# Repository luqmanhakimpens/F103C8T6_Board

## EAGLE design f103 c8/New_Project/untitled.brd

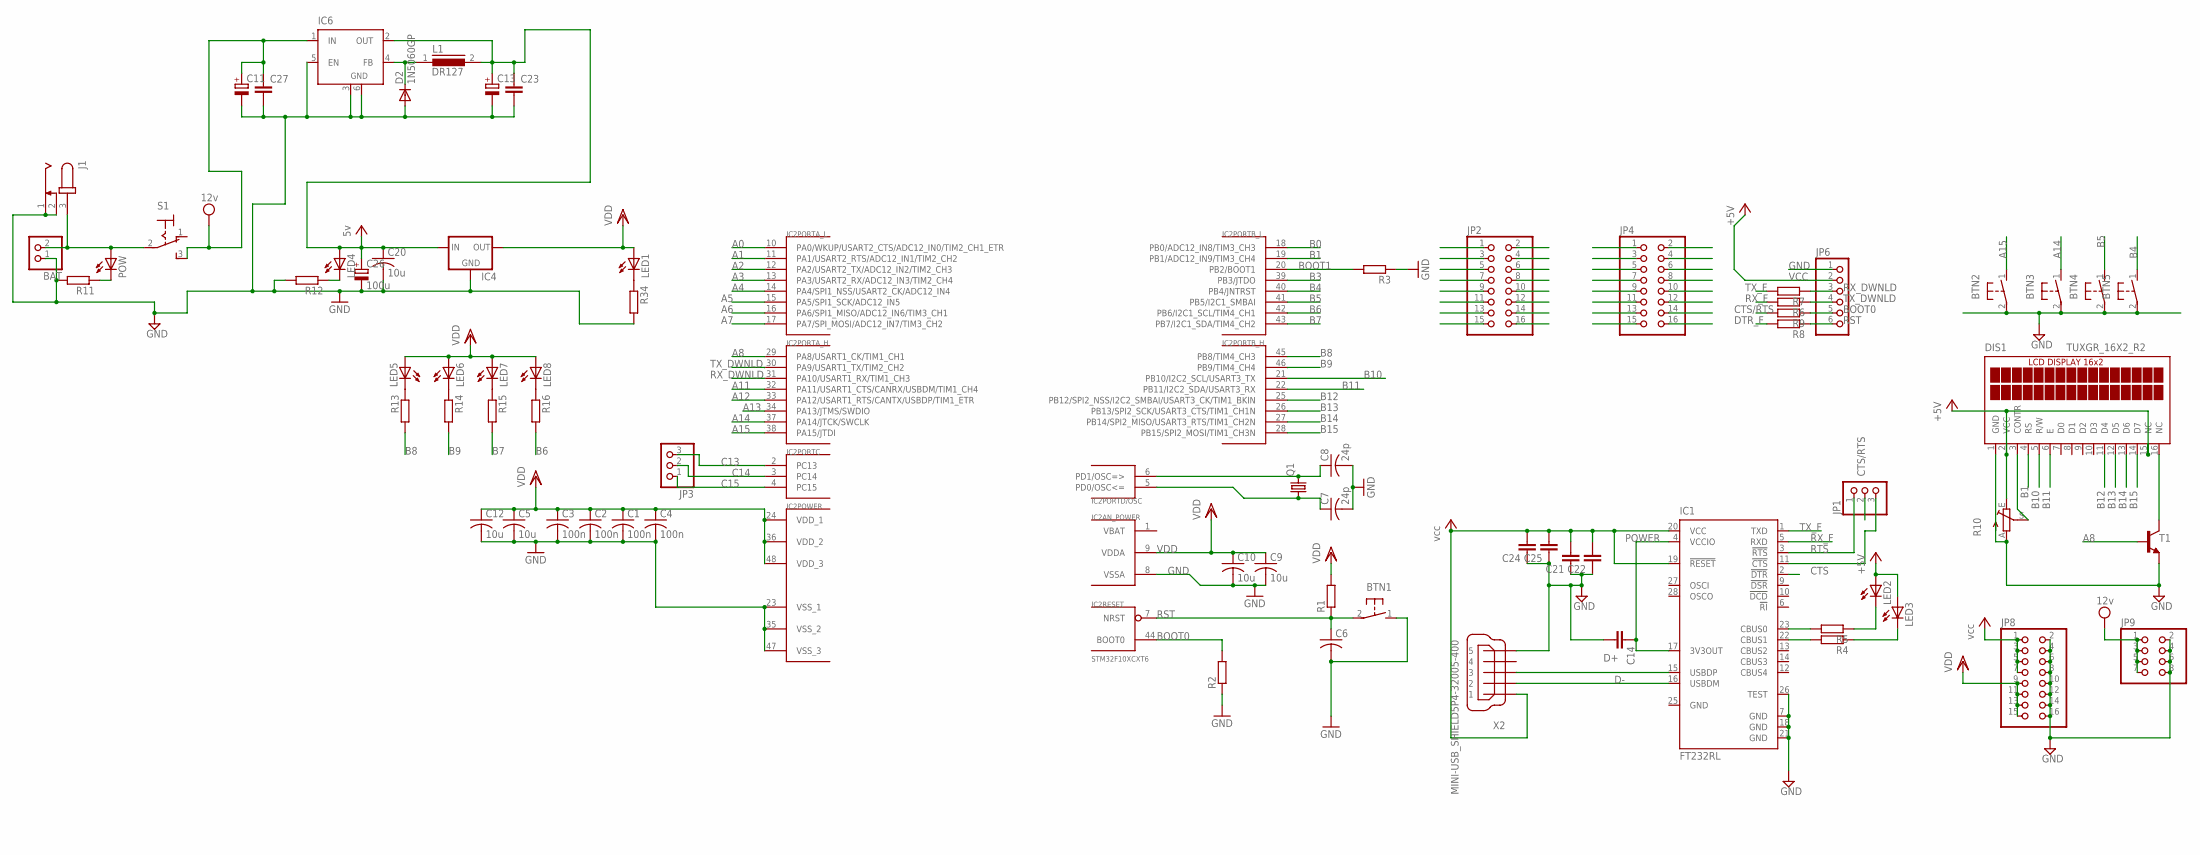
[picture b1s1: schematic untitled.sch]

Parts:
BAT: PINHD-1X2; 1X02
BTN1, BTN2, BTN3, BTN4, BTN5: PUSHBTN; PUSHBUTTON
C1, C2, C3, C4: 100n; C0805
C5, C9, C10, C12, C20: 10u; C0805
C6: C-USC0805; C0805
C7, C8: 24p; C0805
C11, C13: CPOL-EU153CLV-1012; 153CLV-1012
C14, C21, C22, C23, C24, C25, C27: C-EUC0805; C0805
C26: 100u; 153CLV-1012
D2: 1N5060GP; DO15-12
DIS1: TUXGR_16X2_R2
IC1: FT232RL; SSOP28
IC2: STM32F10XCXT6; TQFP48
IC4: LM1117; SOT223
IC6: LM2596S; TO263-5
J1: JACK-PLUG1; SPC4078
JP1, JP3: PINHD-1X3; 1X03
JP2, JP4, JP8: PINHD-2X8; 2X08
JP6: PINHD-1X6; 1X06
JP9: PINHD-2X4; 2X04
L1: DR127
LED1, LED2, LED3, LED4, LED5, LED6, LED7, LED8: LEDSMT1206; 1206
POW: LEDSMT1206; 1206
Q1: CRYSTALHC49U-V; HC49U-V
R1, R2, R3, R11, R12, R13, R14, R15, R16, R34: R-EU_M0805; M0805
R4, R5, R6, R7, R8, R9: R-EU_R0805; R0805
R10: TRIM_EU-CA6V; CA6V
S1: 320-916
T1: BC818-NPN-SOT23-BEC; SOT23-BEC
X2: MINI-USB_SHIELD5P4-32005-400; 32005-400

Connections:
12V: C11.+, C27.1, IC6.1 (IN), JP9.1, JP9.3, JP9.5, JP9.7, S1.3 (S)
A0: IC2.10 (PA0/WKUP/USART2_CTS/ADC12_IN0/TIM2_CH1_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)
A1: IC2.11 (PA1/USART2_RTS/ADC12_IN1/TIM2_CH2)
A2: IC2.12 (PA2/USART2_TX/ADC12_IN2/TIM2_CH3)
A3: IC2.13 (PA3/USART2_RX/ADC12_IN3/TIM2_CH4)
A4: IC2.14 (PA4/SPI1_NSS/USART2_CK/ADC12_IN4)
A5: IC2.15 (PA5/SPI1_SCK/ADC12_IN5)
A6: IC2.16 (PA6/SPI1_MISO/ADC12_IN6/TIM3_CH1)
A7: IC2.17 (PA7/SPI_MOSI/ADC12_IN7/TIM3_CH2)
A8: IC2.29 (PA8/USART1_CK/TIM1_CH1), T1.B
A11: IC2.32 (PA11/USART1_CTS/CANRX/USBDM/TIM1_CH4)
A12: IC2.33 (PA12/USART1_RTS/CANTX/USBDP/TIM1_ETR)
A13: IC2.34 (PA13/JTMS/SWDIO)
A14: BTN3.1, IC2.37 (PA14/JTCK/SWCLK)
A15: BTN2.1, IC2.38 (PA15/JTDI)
B0: IC2.18 (PB0/ADC12_IN8/TIM3_CH3)
B1: DIS1.4 (RS), IC2.19 (PB1/ADC12_IN9/TIM3_CH4)
B3: IC2.39 (PB3/JTDO)
B4: BTN5.1, IC2.40 (PB4/JNTRST)
B5: BTN4.1, IC2.41 (PB5/I2C1_SMBAI)
B6: IC2.42 (PB6/I2C1_SCL/TIM4_CH1), R16.2
B7: IC2.43 (PB7/I2C1_SDA/TIM4_CH2), R15.2
B8: IC2.45 (PB8/TIM4_CH3), R13.2
B9: IC2.46 (PB9/TIM4_CH4), R14.2
B10: DIS1.5 (R/W), IC2.21 (PB10/I2C2_SCL/USART3_TX)
B11: DIS1.6 (E), IC2.22 (PB11/I2C2_SDA/USART3_RX)
B12: DIS1.11 (D4), IC2.25 (PB12/SPI2_NSS/I2C2_SMBAI/USART3_CK/TIM1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)
B13: DIS1.12 (D5), IC2.26 (PB13/SPI2_SCK/USART3_CTS/TIM1_CH1N)
B14: DIS1.13 (D6), IC2.27 (PB14/SPI2_MISO/USART3_RTS/TIM1_CH2N)
B15: DIS1.14 (D7), IC2.28 (PB15/SPI2_MOSI/TIM1_CH3N)
BOOT0: IC2.44 (BOOT0), JP6.5, R2.2, R9.1
BOOT1: IC2.20 (PB2/BOOT1), R3.2
C13: IC2.2 (PC13), JP3.3
C14: IC2.3 (PC14), JP3.2
C15: IC2.4 (PC15), JP3.1
CTS: IC1.11 (!CTS), JP1.3
CTS/RTS: JP1.2, R9.2
D+: IC1.15 (USBDP), X2.3
D-: IC1.16 (USBDM), X2.2
DTR_F: IC1.2 (!DTR), R8.2
GND: BAT.1, BTN1.1, BTN2.2, BTN3.2, BTN4.2, BTN5.2, C1.2, C2.2, C3.2, C4.2, C5.2, C6.2, C7.2, C8.2, C9.2, C10.2, C11.-, C12.2, C13.-, C14.2, C20.2, C21.1, C22.1, C23.2, C24.1, C25.1, C26.-, C27.2, D2.A, DIS1.1 (GND), IC1.7 (GND), IC1.18 (GND), IC1.21 (GND), IC1.25 (GND), IC1.26 (TEST), IC2.8 (VSSA), IC2.23 (VSS_1), IC2.35 (VSS_2), IC2.47 (VSS_3), IC4.1 (GND), IC6.3 (GND), IC6.5 (EN), IC6.6 (GND), J1.1, J1.2, JP6.1, JP8.2, JP8.4, JP8.6, JP8.8, JP8.10, JP8.12, JP8.14, JP8.16, JP9.2, JP9.4, JP9.6, JP9.8, R2.1, R3.1, R10.A, R11.2, R12.2, R34.2, T1.E, X2.5
unnamed: LED2.C, R5.1
unnamed: LED3.C, R4.1
unnamed: BAT.2, J1.3, POW.A, S1.2
unnamed: IC1.23 (CBUS0), R5.2
unnamed: IC1.22 (CBUS1), R4.2
unnamed: LED4.C, R12.1
unnamed: DIS1.3 (CONTR), R10.S
unnamed: LED5.C, R13.1
unnamed: LED6.C, R14.1
unnamed: LED7.C, R15.1
unnamed: LED8.C, R16.1
unnamed: DIS1.16 (NC), T1.C
unnamed: D2.C, IC6.4 (FB), L1.1
unnamed: POW.C, R11.1
unnamed: LED1.C, R34.1
OSC_IN: C7.1, IC2.5 (PD0/OSC<=), Q1.1
OSC_OUT: C8.1, IC2.6 (PD1/OSC=>), Q1.2
POWER: C14.1, IC1.4 (VCCIO), IC1.17 (3V3OUT)
RST: BTN1.2, C6.1, IC2.7 (NRST), JP6.6, R1.1, R8.1
RTS: IC1.3 (!RTS), JP1.1
RX_DWNLD: IC2.31 (PA10/USART1_RX/TIM1_CH3), JP6.3, R7.1
RX_F: IC1.5 (RXD), R6.2
TX_DWNLD: IC2.30 (PA9/USART1_TX/TIM2_CH2), JP6.4, R6.1
TX_F: IC1.1 (TXD), R7.2
VBAT: IC2.1 (VBAT)
VCC: C13.+, C20.1, C21.2, C22.2, C23.1, C24.2, C25.2, C26.+, IC1.19 (!RESET), IC1.20 (VCC), IC4.3 (IN), IC6.2 (OUT), JP6.2, JP8.1, JP8.3, JP8.5, JP8.7, L1.2, LED2.A, LED3.A, LED4.A, X2.1
VDD: C1.1, C2.1, C3.1, C4.1, C5.1, C9.1, C10.1, C12.1, DIS1.2 (VCC), DIS1.15 (NC), IC2.9 (VDDA), IC2.24 (VDD_1), IC2.36 (VDD_2), IC2.48 (VDD_3), IC4.2 (OUT), JP8.9, JP8.11, JP8.13, JP8.15, LED1.A, LED5.A, LED6.A, LED7.A, LED8.A, R1.2, R10.E

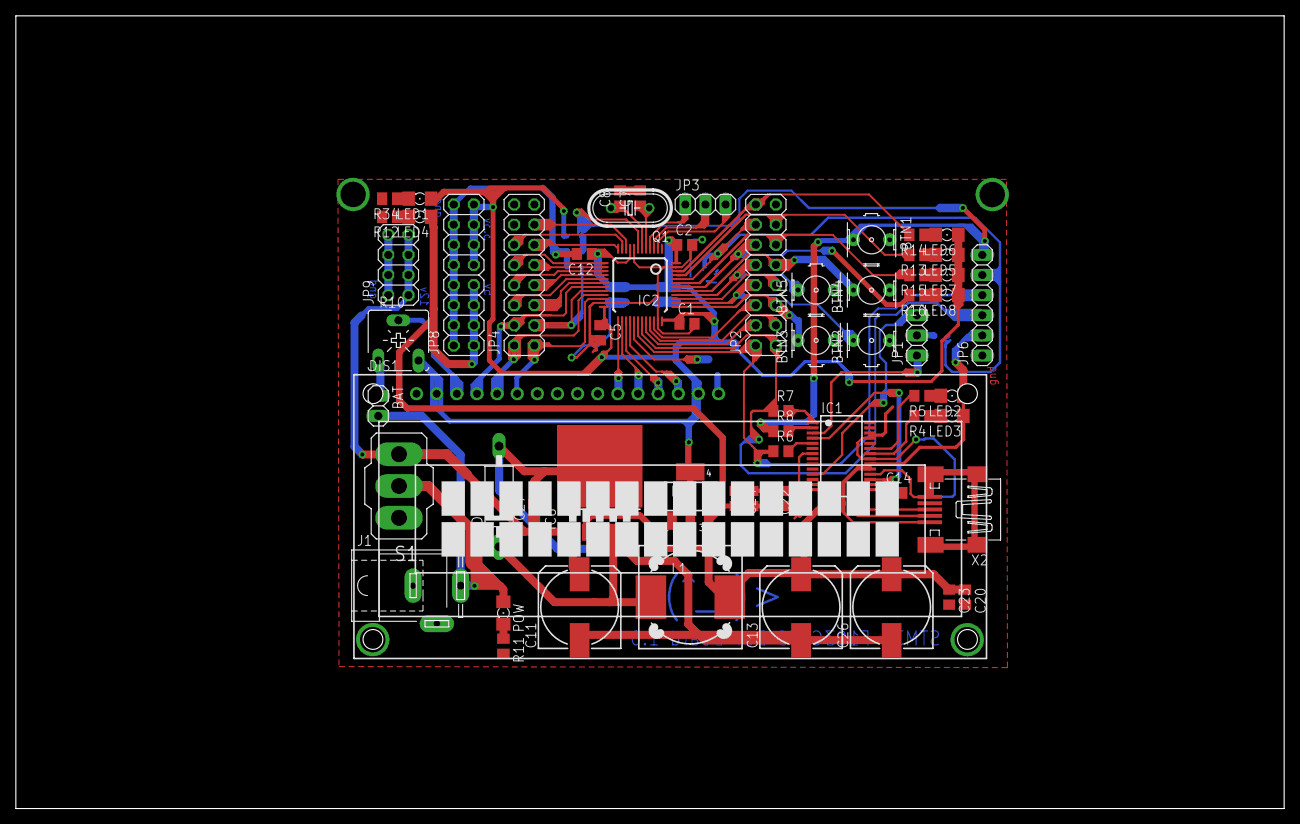
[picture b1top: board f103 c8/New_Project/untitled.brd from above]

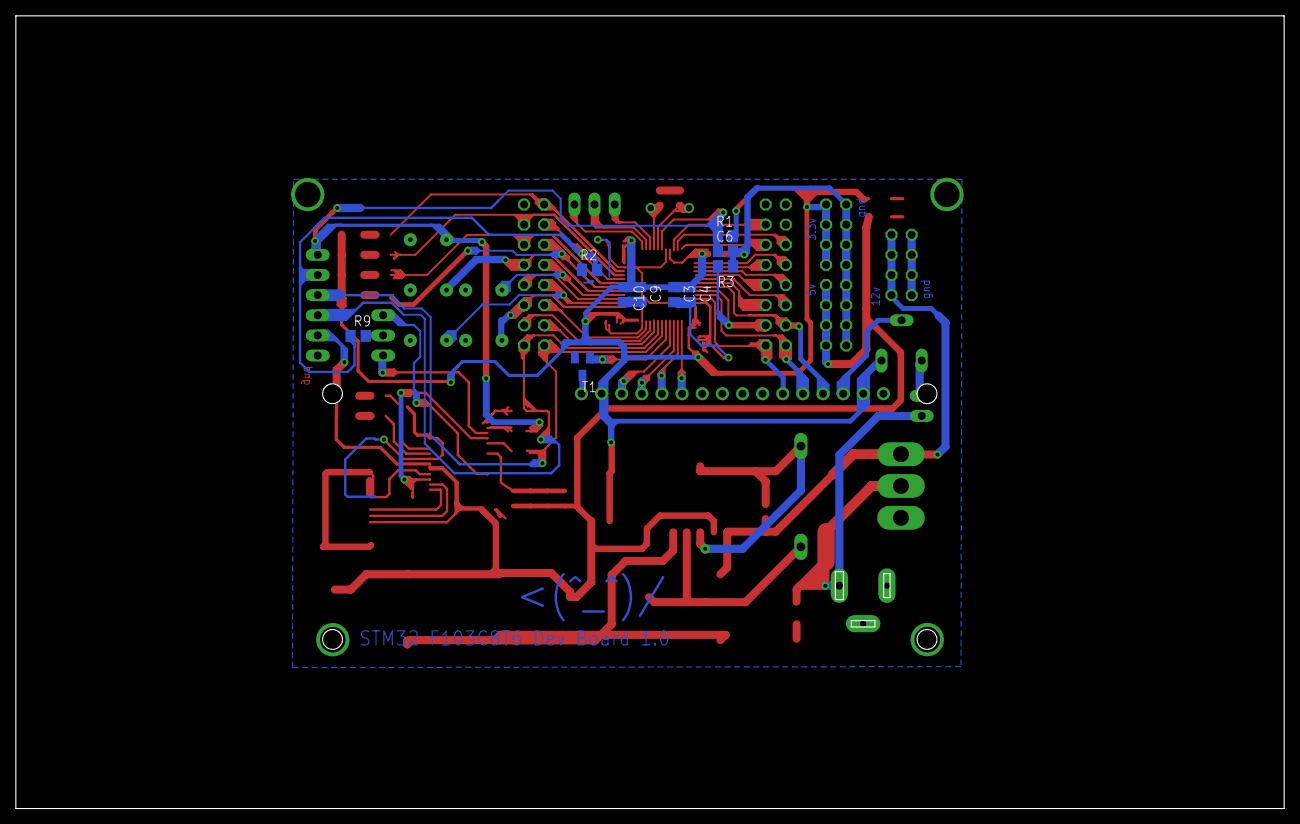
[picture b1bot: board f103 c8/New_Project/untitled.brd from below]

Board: 2 copper layers, 160.0 x 100.0 mm, 73 parts (10 on the bottom side), 54 nets.

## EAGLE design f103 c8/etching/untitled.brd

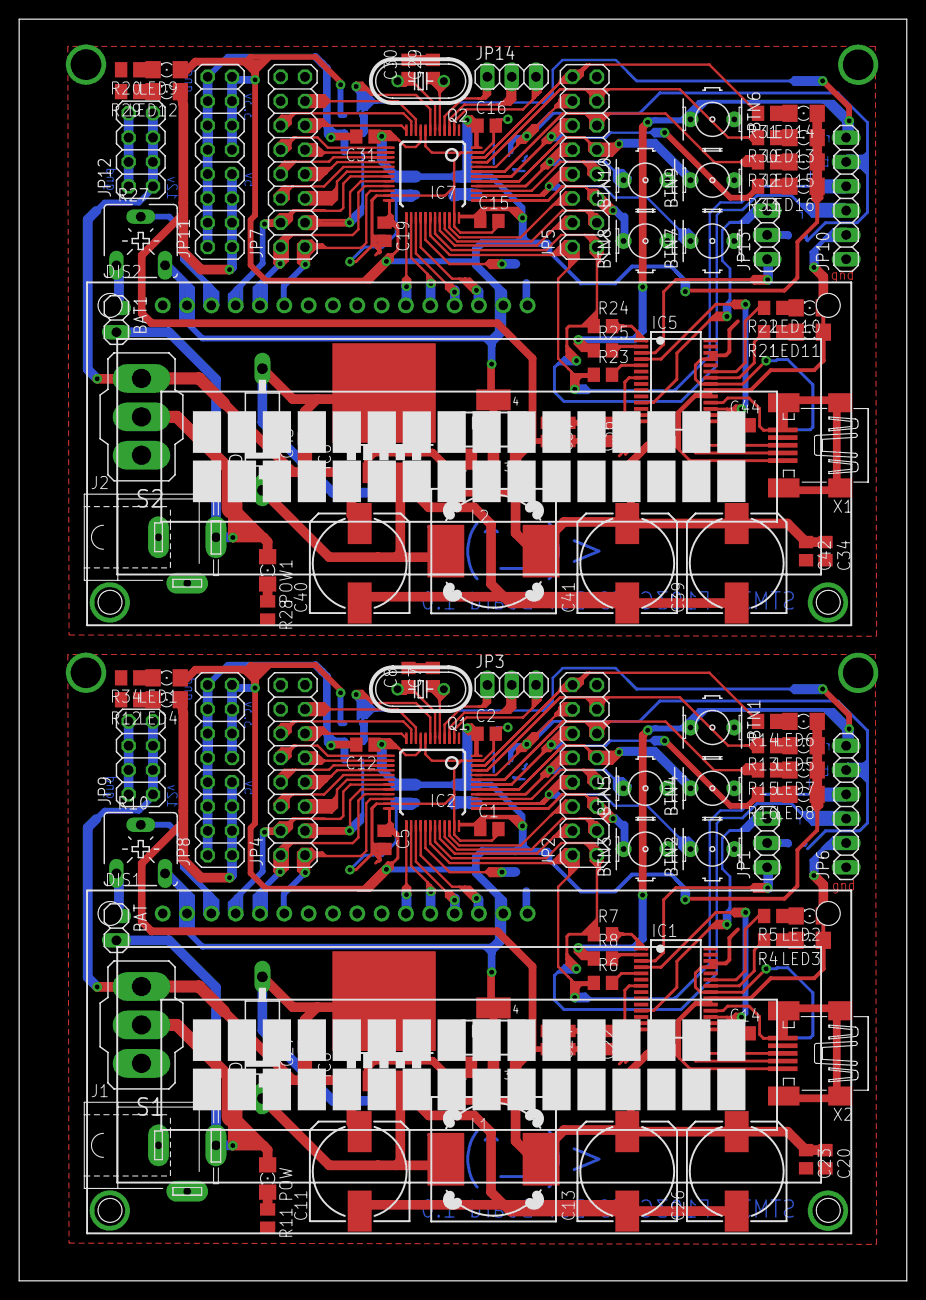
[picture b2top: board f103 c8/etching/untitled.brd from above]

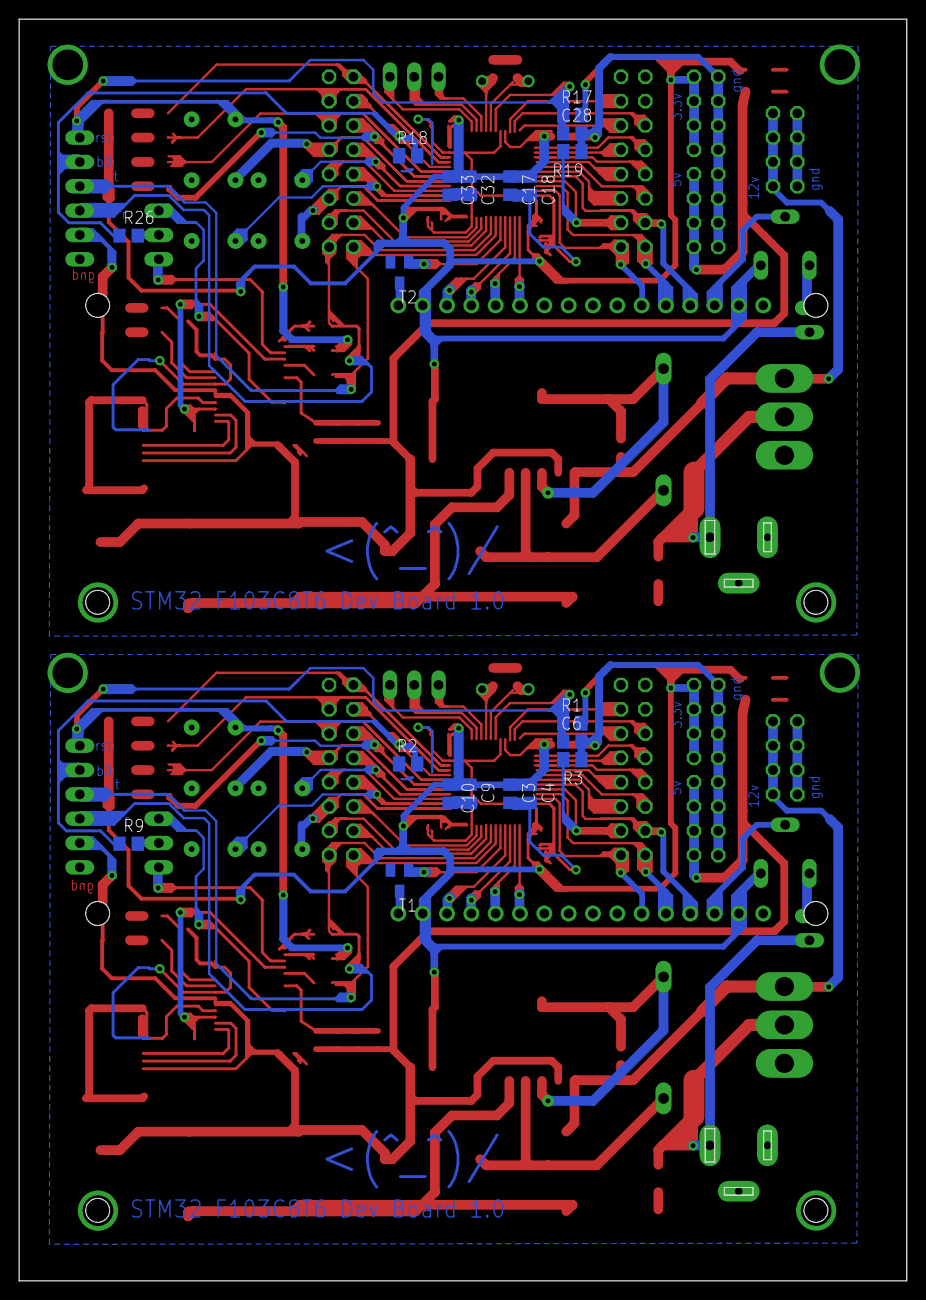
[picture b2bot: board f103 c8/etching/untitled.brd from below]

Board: 2 copper layers, 92.7 x 131.8 mm, 146 parts (20 on the bottom side), 108 nets.

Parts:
BAT, BAT1: 1X02
BTN1, BTN2, BTN3, BTN4, BTN5, BTN6, BTN7, BTN8, BTN9, BTN10: PUSHBTN; PUSHBUTTON
C1, C2, C3, C4, C15, C16, C17, C18: 100n; C0805
C5, C9, C10, C12, C19, C20, C31, C32, C33, C34: 10u; C0805
C6, C14, C21, C22, C23, C24, C25, C27, C28, C35, C36, C37, C38, C42, C43, C44: C0805
C7, C8, C29, C30: 24p; C0805
C11, C13, C40, C41: 153CLV-1012
C26, C39: 100u; 153CLV-1012
D1, D2: 1N5060GP; DO15-12
DIS1, DIS2: TUXGR_16X2_R2
IC1, IC5: FT232RL; SSOP28
IC2, IC7: STM32F10XCXT6; TQFP48
IC3, IC4: SOT223
IC6, IC8: TO263-5
J1, J2: SPC4078
JP1, JP3, JP13, JP14: 1X03
JP2, JP4, JP5, JP7, JP8, JP11: 2X08
JP6, JP10: 1X06
JP9, JP12: 2X04
L1, L2: DR127
LED1, LED2, LED3, LED4, LED5, LED6, LED7, LED8, LED9, LED10, LED11, LED12, LED13, LED14, LED15, LED16: 1206
POW, POW1: 1206
Q1, Q2: HC49U-V
R1, R2, R3, R11, R12, R13, R14, R15, R16, R17, R18, R19, R20, R28, R29, R30, R31, R32, R33, R34: M0805
R4, R5, R6, R7, R8, R9, R21, R22, R23, R24, R25, R26: R0805
R10, R27: CA6V
S1, S2: 320-916
T1, T2: SOT23-BEC
X1, X2: MINI-USB_SHIELD5P4-32005-400; 32005-400

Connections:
12V: C11.+, C27.1, IC6.1, JP9.1, JP9.3, JP9.5, JP9.7, S1.3
12V1: C40.+, C43.1, IC8.1, JP12.1, JP12.3, JP12.5, JP12.7, S2.3
A8: IC2.29, T1.B
A14: BTN3.1, IC2.37
A15: BTN2.1, IC2.38
A21: IC7.29, T2.B
A25: BTN8.1, IC7.37
A26: BTN7.1, IC7.38
B1: DIS1.4, IC2.19
B2: DIS2.5, IC7.21
B4: BTN5.1, IC2.40
B5: BTN4.1, IC2.41
B6: IC2.42, R16.2
B7: IC2.43, R15.2
B8: IC2.45, R13.2
B9: IC2.46, R14.2
B10: DIS1.5, IC2.21
B11: DIS1.6, IC2.22
B12: DIS1.11, IC2.25
B13: DIS1.12, IC2.26
B14: DIS1.13, IC2.27
B15: DIS1.14, IC2.28
B16: IC7.45, R30.2
B17: IC7.46, R31.2
B18: DIS2.11, IC7.25
B19: DIS2.12, IC7.26
B20: DIS2.13, IC7.27
B21: DIS2.14, IC7.28
B23: DIS2.4, IC7.19
B25: BTN10.1, IC7.40
B26: BTN9.1, IC7.41
B27: IC7.42, R33.2
B28: IC7.43, R32.2
B29: DIS2.6, IC7.22
BOOT0: IC2.44, JP6.5, R2.2, R9.1
BOOT1: IC2.20, R3.2
BOOT2: IC7.44, JP10.5, R18.2, R26.1
BOOT3: IC7.20, R19.2
C1: IC7.2, JP14.3
C2: IC7.3, JP14.2
C3: IC7.4, JP14.1
C13: IC2.2, JP3.3
C14: IC2.3, JP3.2
C15: IC2.4, JP3.1
CTS: IC1.11, JP1.3
CTS1: IC5.11, JP13.3
CTS/RTS: JP1.2, R9.2
CTS/RTS1: JP13.2, R26.2
D+: IC1.15, X2.3
D+1: IC5.15, X1.3
D-: IC1.16, X2.2
D-1: IC5.16, X1.2
DTR_F: IC1.2, R8.2
DTR_F1: IC5.2, R25.2
GND: BAT.1, BTN1.1, BTN2.2, BTN3.2, BTN4.2, BTN5.2, C1.2, C2.2, C3.2, C4.2, C5.2, C6.2, C7.2, C8.2, C9.2, C10.2, C11.-, C12.2, C13.-, C14.2, C20.2, C21.1, C22.1, C23.2, C24.1, C25.1, C26.-, C27.2, D2.A, DIS1.1, IC1.7, IC1.18, IC1.21, IC1.25, IC1.26, IC2.8, IC2.23, IC2.35, IC2.47, IC4.1, IC6.3, IC6.5, IC6.6, J1.1, J1.2, JP6.1, JP8.2, JP8.4, JP8.6, JP8.8, JP8.10, JP8.12, JP8.14, JP8.16, JP9.2, JP9.4, JP9.6, JP9.8, R2.1, R3.1, R10.A, R11.2, R12.2, R34.2, T1.E, X2.5
GND1: BAT1.1, BTN6.1, BTN7.2, BTN8.2, BTN9.2, BTN10.2, C15.2, C16.2, C17.2, C18.2, C19.2, C28.2, C29.2, C30.2, C31.2, C32.2, C33.2, C34.2, C35.1, C36.1, C37.1, C38.1, C39.-, C40.-, C41.-, C42.2, C43.2, C44.2, D1.A, DIS2.1, IC3.1, IC5.7, IC5.18, IC5.21, IC5.25, IC5.26, IC7.8, IC7.23, IC7.35, IC7.47, IC8.3, IC8.5, IC8.6, J2.1, J2.2, JP10.1, JP11.2, JP11.4, JP11.6, JP11.8, JP11.10, JP11.12, JP11.14, JP11.16, JP12.2, JP12.4, JP12.6, JP12.8, R18.1, R19.1, R20.2, R27.A, R28.2, R29.2, T2.E, X1.5
unnamed: LED2.C, R5.1
unnamed: LED3.C, R4.1
unnamed: BAT.2, J1.3, POW.A, S1.2
unnamed: IC1.23, R5.2
unnamed: IC1.22, R4.2
unnamed: LED4.C, R12.1
unnamed: DIS1.3, R10.S
unnamed: LED5.C, R13.1
unnamed: LED6.C, R14.1
unnamed: LED7.C, R15.1
unnamed: LED8.C, R16.1
unnamed: DIS1.16, T1.C
unnamed: D2.C, IC6.4, L1.1
unnamed: POW.C, R11.1
unnamed: LED1.C, R34.1
unnamed: LED9.C, R20.1
unnamed: IC5.23, R22.2
unnamed: IC5.22, R21.2
unnamed: LED10.C, R22.1
unnamed: LED11.C, R21.1
unnamed: DIS2.3, R27.S
unnamed: DIS2.16, T2.C
unnamed: POW1.C, R28.1
unnamed: BAT1.2, J2.3, POW1.A, S2.2
unnamed: LED12.C, R29.1
unnamed: LED13.C, R30.1
unnamed: LED14.C, R31.1
unnamed: LED15.C, R32.1
unnamed: LED16.C, R33.1
unnamed: D1.C, IC8.4, L2.1
OSC_IN: C7.1, IC2.5, Q1.1
OSC_IN1: C29.1, IC7.5, Q2.1
OSC_OUT: C8.1, IC2.6, Q1.2
OSC_OUT1: C30.1, IC7.6, Q2.2
POWER: C14.1, IC1.4, IC1.17
POWER1: C44.1, IC5.4, IC5.17
RST: BTN1.2, C6.1, IC2.7, JP6.6, R1.1, R8.1
RST1: BTN6.2, C28.1, IC7.7, JP10.6, R17.1, R25.1
RTS: IC1.3, JP1.1
RTS1: IC5.3, JP13.1
RX_DWNLD: IC2.31, JP6.3, R7.1
RX_DWNLD1: IC7.31, JP10.3, R24.1
RX_F: IC1.5, R6.2
RX_F1: IC5.5, R23.2
TX_DWNLD: IC2.30, JP6.4, R6.1
TX_DWNLD1: IC7.30, JP10.4, R23.1
TX_F: IC1.1, R7.2
TX_F1: IC5.1, R24.2
VCC: C13.+, C20.1, C21.2, C22.2, C23.1, C24.2, C25.2, C26.+, IC1.19, IC1.20, IC4.3, IC6.2, JP6.2, JP8.1, JP8.3, JP8.5, JP8.7, L1.2, LED2.A, LED3.A, LED4.A, X2.1
VCC1: C34.1, C35.2, C36.2, C37.2, C38.2, C39.+, C41.+, C42.1, IC3.3, IC5.19, IC5.20, IC8.2, JP10.2, JP11.1, JP11.3, JP11.5, JP11.7, L2.2, LED10.A, LED11.A, LED12.A, X1.1
VDD: C1.1, C2.1, C3.1, C4.1, C5.1, C9.1, C10.1, C12.1, DIS1.2, DIS1.15, IC2.9, IC2.24, IC2.36, IC2.48, IC4.2, JP8.9, JP8.11, JP8.13, JP8.15, LED1.A, LED5.A, LED6.A, LED7.A, LED8.A, R1.2, R10.E
VDD1: C15.1, C16.1, C17.1, C18.1, C19.1, C31.1, C32.1, C33.1, DIS2.2, DIS2.15, IC3.2, IC7.9, IC7.24, IC7.36, IC7.48, JP11.9, JP11.11, JP11.13, JP11.15, LED9.A, LED13.A, LED14.A, LED15.A, LED16.A, R17.2, R27.E

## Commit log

2018-07-29 init
